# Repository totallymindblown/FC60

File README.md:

# **FC60**
A simple Feeder Controller for electric SMT-Feeders.

## Specifications
* reliable Atmel SAMC21N18A MCU
* single 24V Power Supply
* max. 60 Feeders can be controlled with one Board
* CAN-FD Interface (compatible with MB6HC, MB6XD, etc.)
* optional RS485 Interface
## Hardware
The board has been designed with [Kicad 8.0.4](https://www.kicad.org).  
All schematics, design-files, gerbers and bom can be found in [hardware](/hardware/).
## Software
A Bootloader and Firmware for use with e.g. RFF 3.5 can be found in [Releases](http://github.com/totallymindblown/FC60/releases/latest).  

First the bootloader needs to be programmed with a suitable programmer (e.g. ATMEL-ICE, SEGGER J-Link, etc.) using the SWD-Interface J61 (10-pin 50mil connector), then the firmware can be uploaded from the mainboard. Since the MCU runs with 5V, the programmer must support this target voltage.
## How to Use
The feeders are each connected using connector J1..J60 and supplied with 24V. The trigger signal is provided by a short pulse (1 ms) to the control input of the feeder.
An appropriately dimensioned 24V switching power supply is connected to J64.

To be able to trigger the feeders, a single GPIO pin must be created for the FC60 using the following gcode example. The port number and CAN address are selected according to the application.

*_create Port 12 on FC60 with CAN address 24 :_* <b>`M950 P12 C"24.feeder"`</b>

The feeder is selected using <b>M42</b> with the <b>S</b> parameter, but it has here nothing to do with PWM. It is just a simple way on the FC60 to circumvent the RFF GPIO limit.  

*_trigger feeder number 1 :_* <b>`M42 P12 S1`</b>  

*_trigger feeder number 60 :_* <b>`M42 P12 S60`</b>  

The default CAN address of the FC60 is 124 which can be reset using JP2 (__CAN-RES__).  
CAN bus termination can be set with jumper JP1 (__TERM.__).

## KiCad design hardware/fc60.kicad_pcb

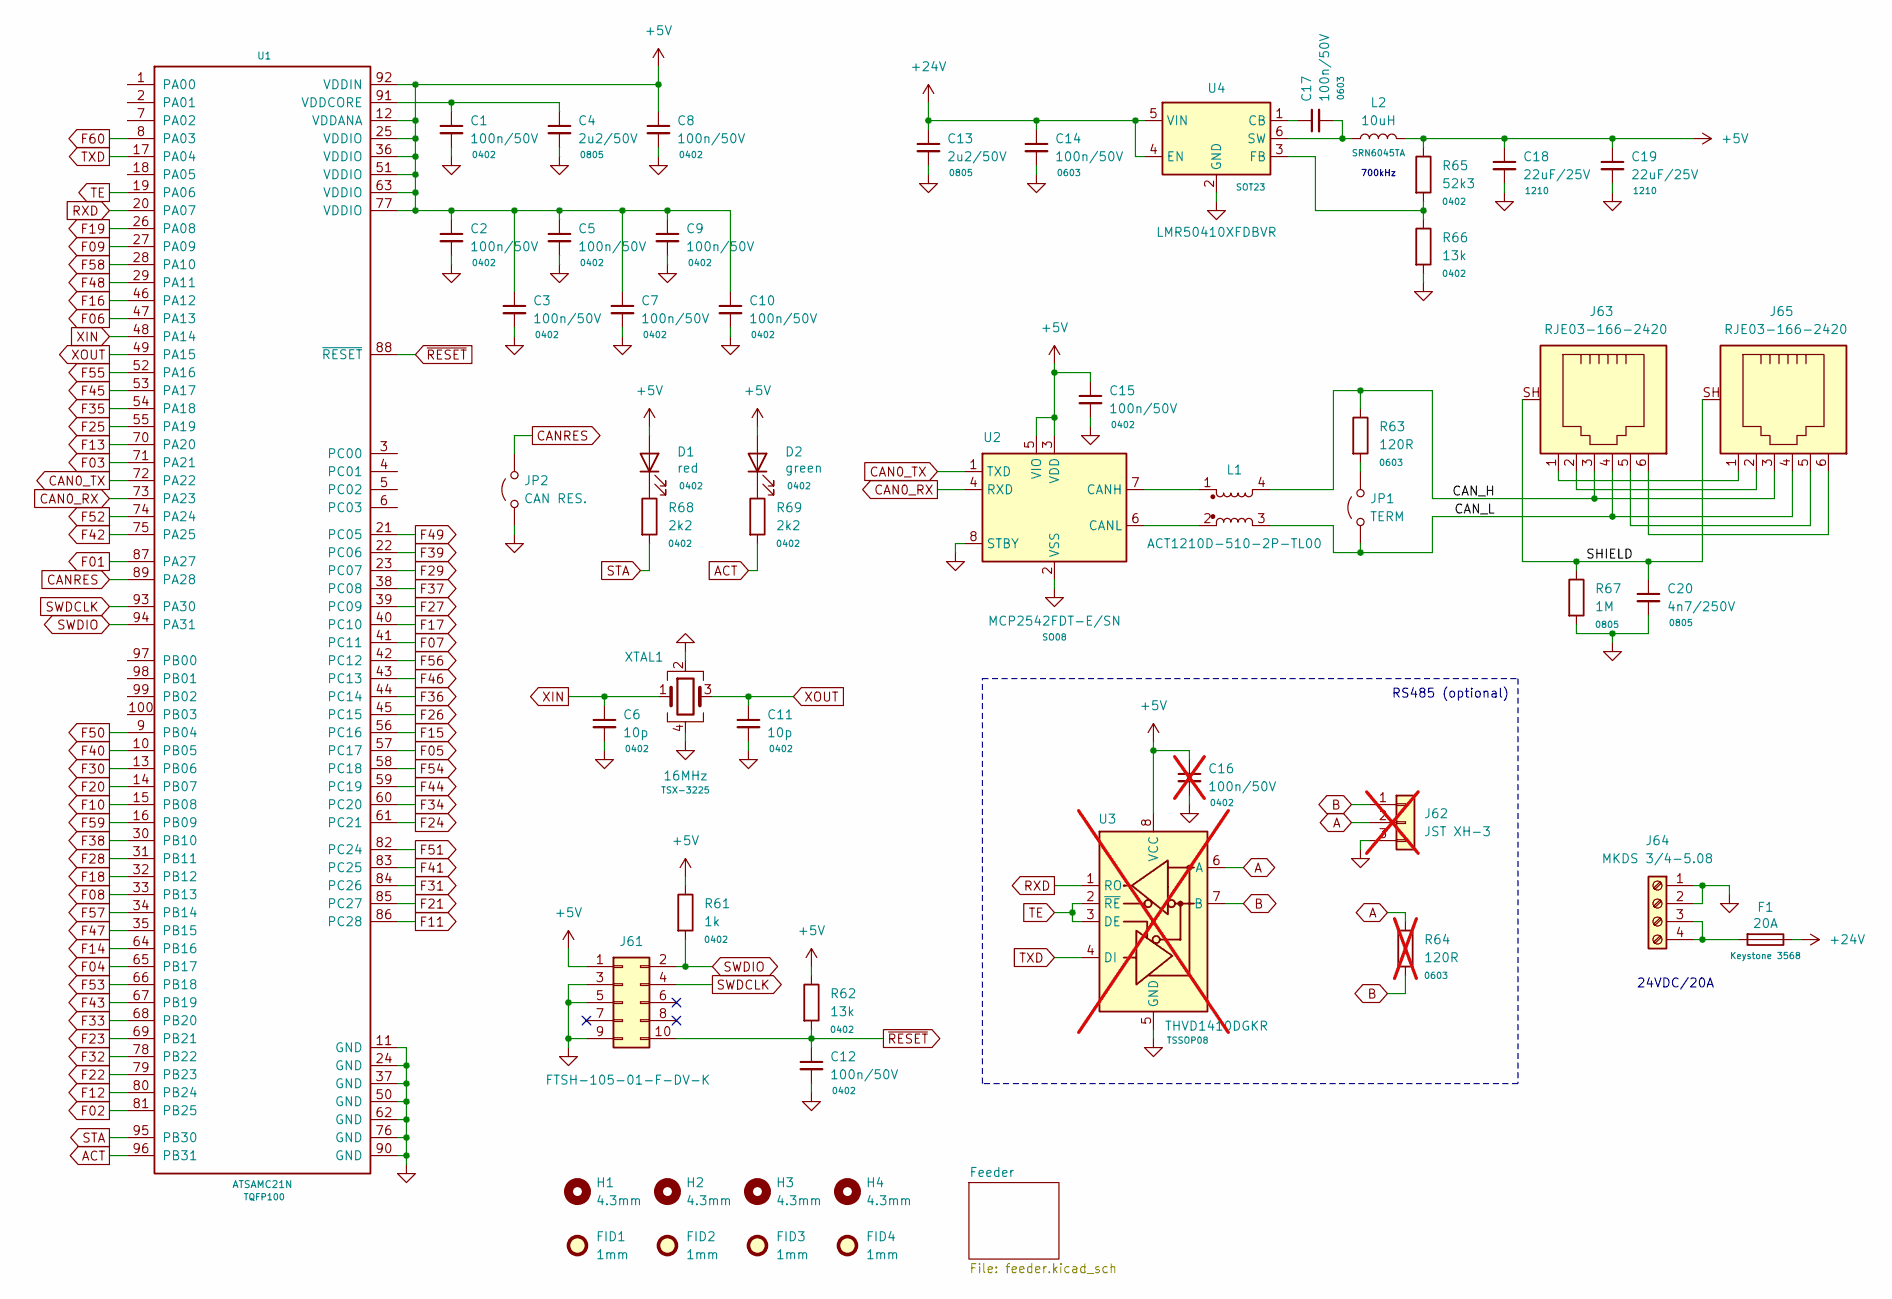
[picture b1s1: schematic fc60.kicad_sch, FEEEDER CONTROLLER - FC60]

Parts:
C1, C2, C3, C5, C7, C8, C9, C10, C12, C15: 100n/50V; C_0402_1005Metric
C4, C13: 2u2/50V; C_0805_2012Metric
C6, C11: 10p; C_0402_1005Metric
C14, C17: 100n/50V; C_0603_1608Metric
C16: 100n/50V; C_0402_1005Metric; not fitted
C18, C19: 22uF/25V; C_1210_3225Metric
C20: 4n7/250V; C_0805_2012Metric
D1: red; LED_0402_1005Metric
D2: green; LED_0402_1005Metric
F1: 20A; Fuseholder_Blade_Mini_Keystone_3568
FID1, FID2, FID3, FID4: 1mm; Fiducial_1mm_Mask2mm
H1, H2, H3, H4: 4.3mm; MountingHole_4.3mm_M4_ISO7380_Pad
J61: FTSH-105-01-F-DV-K; Samtec_SFH-105-01-F-D-K-TR
J62: JST XH-3; JST_XH_B3B-XH-A_1x03_P2.50mm_Vertical; not fitted
J63, J65: RJE03-166-2420; RJ25_Amphenol_RJE031662x20
J64: MKDS 3/4-5.08; TerminalBlock_Phoenix_MKDS-3-4-5.08_1x04_P5.08mm_Horizontal
JP1: TERM; PinHeader_1x02_P2.54mm_Vertical
JP2: CAN RES.; PinHeader_1x02_P2.54mm_Vertical
L1: ACT1210D-510-2P-TL00; L_CommonModeChoke_TDK_ACT1210D
L2: 10uH; L_Bourns_SRN6045TA
R61: 1k; R_0402_1005Metric
R62, R66: 13k; R_0402_1005Metric
R63: 120R; R_0603_1608Metric
R64: 120R; R_0603_1608Metric; not fitted
R65: 52k3; R_0402_1005Metric
R67: 1M; R_0805_2012Metric
R68, R69: 2k2; R_0402_1005Metric
U1: ATSAMC21N; TQFP-100_14x14mm_P0.5mm
U2: MCP2542FDT-E/SN; SO-8_3.9x4.9mm_P1.27mm
U3: THVD1410DGKR; TSSOP-8_3x3mm_P0.65mm; not fitted
U4: LMR50410XFDBVR; SOT-23-6
XTAL1: 16MHz; Crystal_SMD_SeikoEpson_TSX3225-4Pin_3.2x2.5mm

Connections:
+5V: C2.1, C3.1, C5.1, C7.1, C8.1, C9.1, C10.1, C15.1, C16.1, C18.1, C19.1, D1.2 (A), D2.2 (A), J61.1, L2.2, R61.1, R62.1, R65.1, U1.12 (VDDANA), U1.25 (VDDIO), U1.36 (VDDIO), U1.51 (VDDIO), U1.63 (VDDIO), U1.77 (VDDIO), U1.92 (VDDIN), U2.3 (VDD), U2.5 (VIO), U3.8 (VCC)
+24V: C13.1, C14.1, F1.1, U4.4 (EN), U4.5 (VIN); also elsewhere on the board
/CAN_H: J63.3, J65.3, L1.4, R63.1
/CAN_L: J63.4, J65.4, JP1.1 (A), L1.3
/SHIELD: C20.1, J63.SH, J65.SH, R67.1
A: J62.2, R64.1, U3.6 (A)
ACT: R69.2, U1.96 (PB31)
B: J62.1, R64.2, U3.7 (B)
CAN0_RX: U1.73 (PA23), U2.4 (RXD)
CAN0_TX: U1.72 (PA22), U2.1 (TXD)
CANRES: JP2.2 (B), U1.89 (PA28)
F01: U1.87 (PA27); also elsewhere on the board
F02: U1.81 (PB25); also elsewhere on the board
F03: U1.71 (PA21); also elsewhere on the board
F04: U1.65 (PB17); also elsewhere on the board
F05: U1.57 (PC17); also elsewhere on the board
F06: U1.47 (PA13); also elsewhere on the board
F07: U1.41 (PC11); also elsewhere on the board
F08: U1.33 (PB13); also elsewhere on the board
F09: U1.27 (PA09); also elsewhere on the board
F10: U1.15 (PB08); also elsewhere on the board
F11: U1.86 (PC28); also elsewhere on the board
F12: U1.80 (PB24); also elsewhere on the board
F13: U1.70 (PA20); also elsewhere on the board
F14: U1.64 (PB16); also elsewhere on the board
F15: U1.56 (PC16); also elsewhere on the board
F16: U1.46 (PA12); also elsewhere on the board
F17: U1.40 (PC10); also elsewhere on the board
F18: U1.32 (PB12); also elsewhere on the board
F19: U1.26 (PA08); also elsewhere on the board
F20: U1.14 (PB07); also elsewhere on the board
F21: U1.85 (PC27); also elsewhere on the board
F22: U1.79 (PB23); also elsewhere on the board
F23: U1.69 (PB21); also elsewhere on the board
F24: U1.61 (PC21); also elsewhere on the board
F25: U1.55 (PA19); also elsewhere on the board
F26: U1.45 (PC15); also elsewhere on the board
F27: U1.39 (PC09); also elsewhere on the board
F28: U1.31 (PB11); also elsewhere on the board
F29: U1.23 (PC07); also elsewhere on the board
F30: U1.13 (PB06); also elsewhere on the board
F31: U1.84 (PC26); also elsewhere on the board
F32: U1.78 (PB22); also elsewhere on the board
F33: U1.68 (PB20); also elsewhere on the board
F34: U1.60 (PC20); also elsewhere on the board
F35: U1.54 (PA18); also elsewhere on the board
F36: U1.44 (PC14); also elsewhere on the board
F37: U1.38 (PC08); also elsewhere on the board
F38: U1.30 (PB10); also elsewhere on the board
F39: U1.22 (PC06); also elsewhere on the board
F40: U1.10 (PB05); also elsewhere on the board
F41: U1.83 (PC25); also elsewhere on the board
F42: U1.75 (PA25); also elsewhere on the board
F43: U1.67 (PB19); also elsewhere on the board
F44: U1.59 (PC19); also elsewhere on the board
F45: U1.53 (PA17); also elsewhere on the board
F46: U1.43 (PC13); also elsewhere on the board
F47: U1.35 (PB15); also elsewhere on the board
F48: U1.29 (PA11); also elsewhere on the board
F49: U1.21 (PC05); also elsewhere on the board
F50: U1.9 (PB04); also elsewhere on the board
F51: U1.82 (PC24); also elsewhere on the board
F52: U1.74 (PA24); also elsewhere on the board
F53: U1.66 (PB18); also elsewhere on the board
F54: U1.58 (PC18); also elsewhere on the board
F55: U1.52 (PA16); also elsewhere on the board
F56: U1.42 (PC12); also elsewhere on the board
F57: U1.34 (PB14); also elsewhere on the board
F58: U1.28 (PA10); also elsewhere on the board
F59: U1.16 (PB09); also elsewhere on the board
F60: U1.8 (PA03); also elsewhere on the board
GND: C1.2, C2.2, C3.2, C4.2, C5.2, C6.2, C7.2, C8.2, C9.2, C10.2, C11.2, C12.2, C13.2, C14.2, C15.2, C16.2, C18.2, C19.2, C20.2, J61.3, J61.5, J61.9, J62.3, J64.1, J64.2, JP2.1 (A), R66.2, R67.2, U1.11 (GND), U1.24 (GND), U1.37 (GND), U1.50 (GND), U1.62 (GND), U1.76 (GND), U1.90 (GND), U2.2 (VSS), U2.8 (STBY), U3.5 (GND), U4.2 (GND), XTAL1.2, XTAL1.4; also elsewhere on the board
unnamed: D1.1 (K), R68.1
unnamed: D2.1 (K), R69.1
unnamed: J63.1, J65.1
unnamed: J63.2, J65.2
unnamed: J63.5, J65.5
unnamed: J63.6, J65.6
unnamed: F1.2, J64.3, J64.4
unnamed: JP1.2 (B), R63.2
unnamed: C1.1, C4.1, U1.91 (VDDCORE)
unnamed: L1.1, U2.7 (CANH)
unnamed: L1.2, U2.6 (CANL)
unnamed: C17.1, U4.1 (CB)
unnamed: R65.2, R66.1, U4.3 (FB)
unnamed: C17.2, L2.1, U4.6 (SW)
RXD: U1.20 (PA07), U3.1 (RO)
STA: R68.2, U1.95 (PB30)
SWDCLK: J61.4, U1.93 (PA30)
SWDIO: J61.2, R61.2, U1.94 (PA31)
TE: U1.19 (PA06), U3.2 (~RE), U3.3 (DE)
TXD: U1.17 (PA04), U3.4 (DI)
XIN: C6.1, U1.48 (PA14), XTAL1.1
XOUT: C11.1, U1.49 (PA15), XTAL1.3
~RESET: C12.1, J61.10, R62.2, U1.88 (~RESET)

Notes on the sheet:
24VDC/20A
RS485 (optional)
700kHz

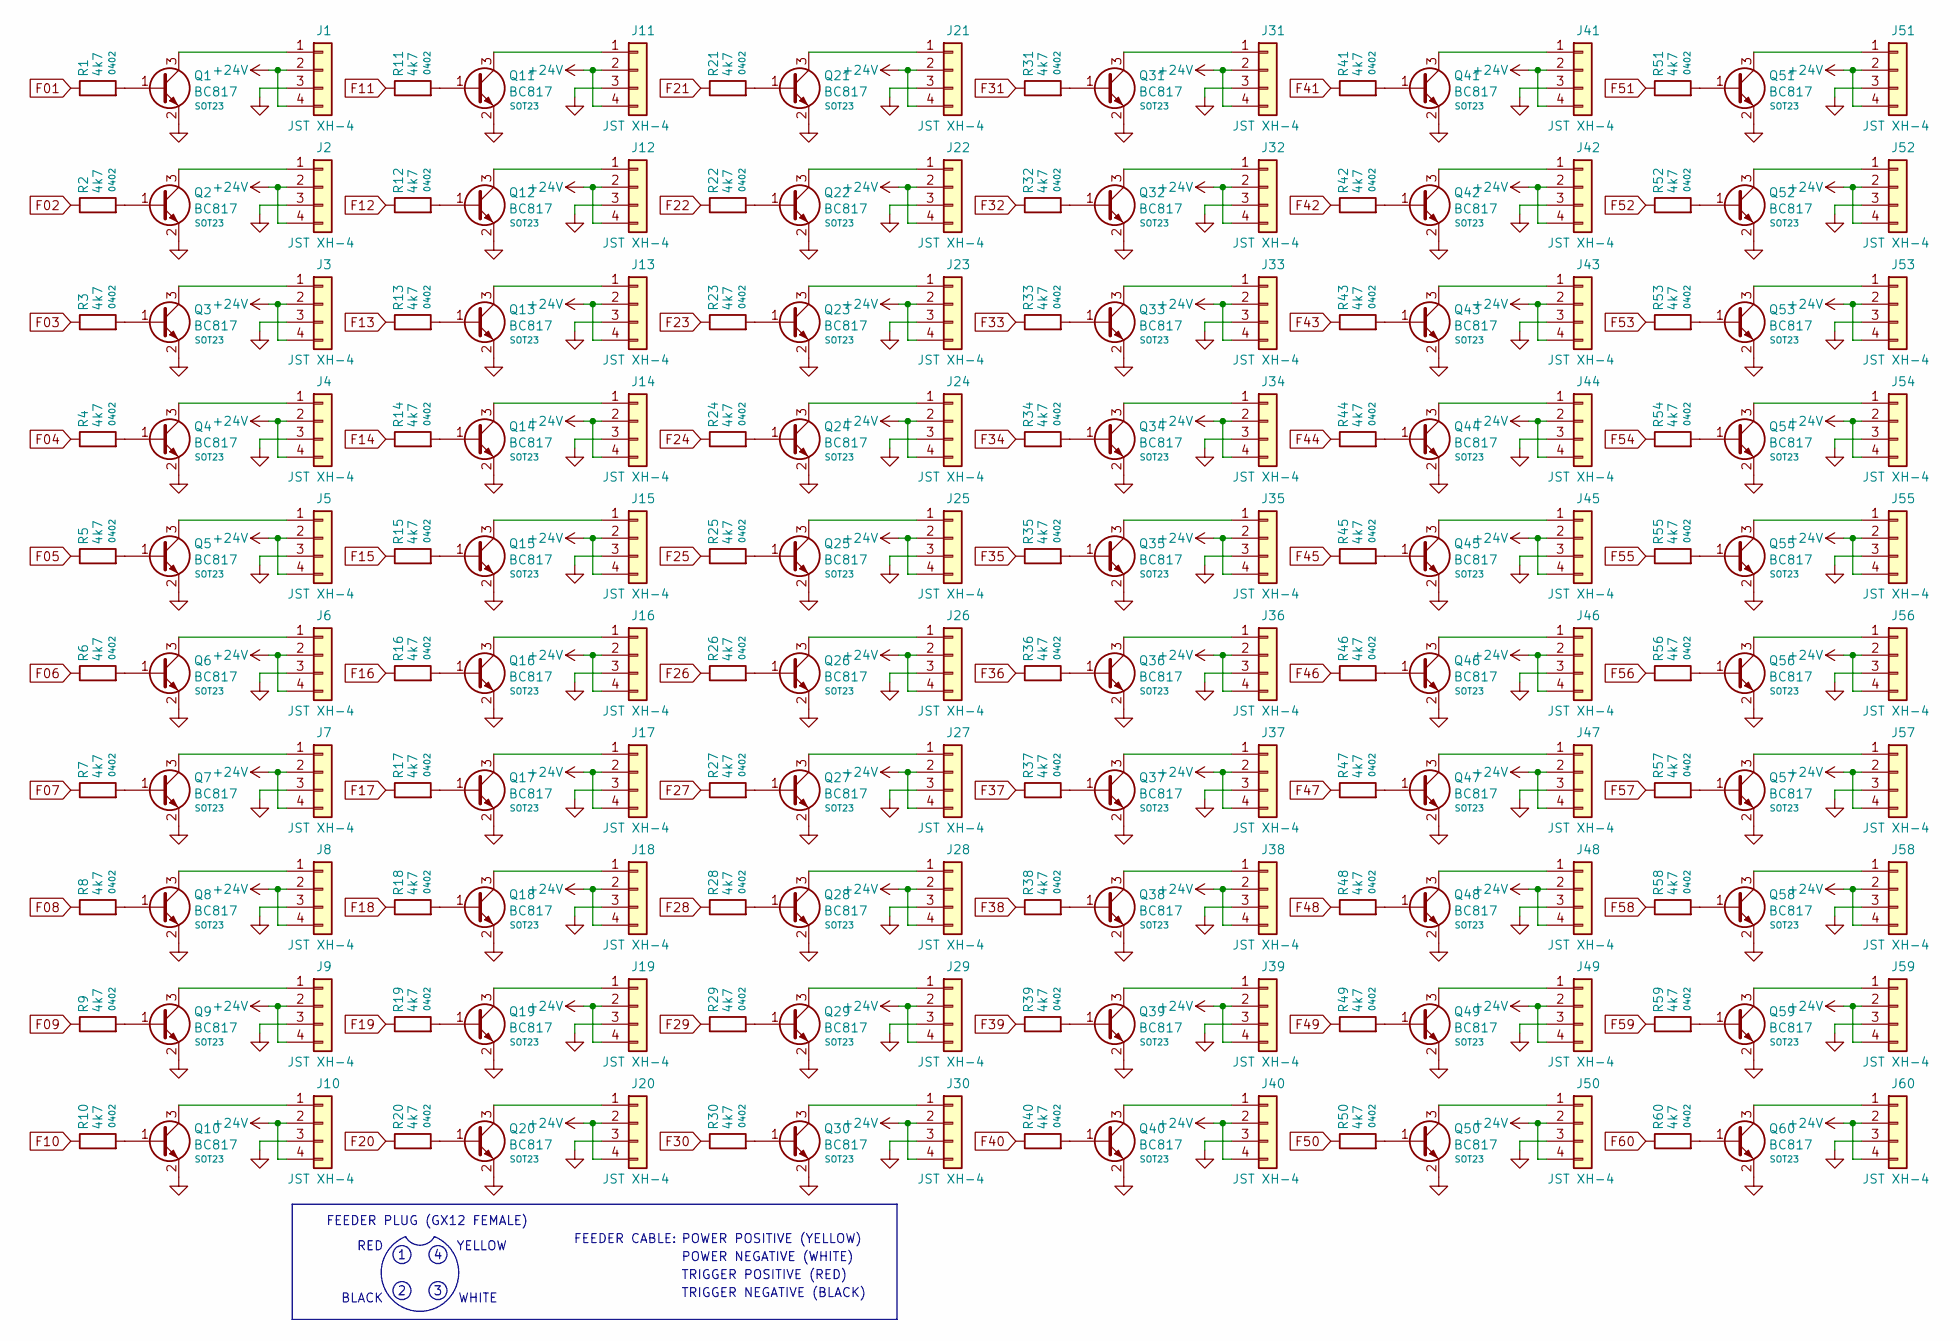
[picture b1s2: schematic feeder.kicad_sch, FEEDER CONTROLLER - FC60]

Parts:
J1, J2, J3, J4, J5, J6, J7, J8, J9, J10, J11, J12, J13, J14, J15, J16, J17, J18, J19, J20, J21, J22, J23, J24, J25, J26, J27, J28, J29, J30, J31, J32, J33, J34, J35, J36, J37, J38, J39, J40, J41, J42, J43, J44, J45, J46, J47, J48, J49, J50, J51, J52, J53, J54, J55, J56, J57, J58, J59, J60: JST XH-4; JST_XH_B4B-XH-A_1x04_P2.50mm_Vertical
Q1, Q2, Q3, Q4, Q5, Q6, Q7, Q8, Q9, Q10, Q11, Q12, Q13, Q14, Q15, Q16, Q17, Q18, Q19, Q20, Q21, Q22, Q23, Q24, Q25, Q26, Q27, Q28, Q29, Q30, Q31, Q32, Q33, Q34, Q35, Q36, Q37, Q38, Q39, Q40, Q41, Q42, Q43, Q44, Q45, Q46, Q47, Q48, Q49, Q50, Q51, Q52, Q53, Q54, Q55, Q56, Q57, Q58, Q59, Q60: BC817; SOT-23
R1, R2, R3, R4, R5, R6, R7, R8, R9, R10, R11, R12, R13, R14, R15, R16, R17, R18, R19, R20, R21, R22, R23, R24, R25, R26, R27, R28, R29, R30, R31, R32, R33, R34, R35, R36, R37, R38, R39, R40, R41, R42, R43, R44, R45, R46, R47, R48, R49, R50, R51, R52, R53, R54, R55, R56, R57, R58, R59, R60: 4k7; R_0402_1005Metric

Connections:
+24V: J1.2, J1.4, J2.2, J2.4, J3.2, J3.4, J4.2, J4.4, J5.2, J5.4, J6.2, J6.4, J7.2, J7.4, J8.2, J8.4, J9.2, J9.4, J10.2, J10.4, J11.2, J11.4, J12.2, J12.4, J13.2, J13.4, J14.2, J14.4, J15.2, J15.4, J16.2, J16.4, J17.2, J17.4, J18.2, J18.4, J19.2, J19.4, J20.2, J20.4, J21.2, J21.4, J22.2, J22.4, J23.2, J23.4, J24.2, J24.4, J25.2, J25.4, J26.2, J26.4, J27.2, J27.4, J28.2, J28.4, J29.2, J29.4, J30.2, J30.4, J31.2, J31.4, J32.2, J32.4, J33.2, J33.4, J34.2, J34.4, J35.2, J35.4, J36.2, J36.4, J37.2, J37.4, J38.2, J38.4, J39.2, J39.4, J40.2, J40.4, J41.2, J41.4, J42.2, J42.4, J43.2, J43.4, J44.2, J44.4, J45.2, J45.4, J46.2, J46.4, J47.2, J47.4, J48.2, J48.4, J49.2, J49.4, J50.2, J50.4, J51.2, J51.4, J52.2, J52.4, J53.2, J53.4, J54.2, J54.4, J55.2, J55.4, J56.2, J56.4, J57.2, J57.4, J58.2, J58.4, J59.2, J59.4, J60.2, J60.4; also elsewhere on the board
F01: R1.1; also elsewhere on the board
F02: R2.1; also elsewhere on the board
F03: R3.1; also elsewhere on the board
F04: R4.1; also elsewhere on the board
F05: R5.1; also elsewhere on the board
F06: R6.1; also elsewhere on the board
F07: R7.1; also elsewhere on the board
F08: R8.1; also elsewhere on the board
F09: R9.1; also elsewhere on the board
F10: R10.1; also elsewhere on the board
F11: R11.1; also elsewhere on the board
F12: R12.1; also elsewhere on the board
F13: R13.1; also elsewhere on the board
F14: R14.1; also elsewhere on the board
F15: R15.1; also elsewhere on the board
F16: R16.1; also elsewhere on the board
F17: R17.1; also elsewhere on the board
F18: R18.1; also elsewhere on the board
F19: R19.1; also elsewhere on the board
F20: R20.1; also elsewhere on the board
F21: R21.1; also elsewhere on the board
F22: R22.1; also elsewhere on the board
F23: R23.1; also elsewhere on the board
F24: R24.1; also elsewhere on the board
F25: R25.1; also elsewhere on the board
F26: R26.1; also elsewhere on the board
F27: R27.1; also elsewhere on the board
F28: R28.1; also elsewhere on the board
F29: R29.1; also elsewhere on the board
F30: R30.1; also elsewhere on the board
F31: R31.1; also elsewhere on the board
F32: R32.1; also elsewhere on the board
F33: R33.1; also elsewhere on the board
F34: R34.1; also elsewhere on the board
F35: R35.1; also elsewhere on the board
F36: R36.1; also elsewhere on the board
F37: R37.1; also elsewhere on the board
F38: R38.1; also elsewhere on the board
F39: R39.1; also elsewhere on the board
F40: R40.1; also elsewhere on the board
F41: R41.1; also elsewhere on the board
F42: R42.1; also elsewhere on the board
F43: R43.1; also elsewhere on the board
F44: R44.1; also elsewhere on the board
F45: R45.1; also elsewhere on the board
F46: R46.1; also elsewhere on the board
F47: R47.1; also elsewhere on the board
F48: R48.1; also elsewhere on the board
F49: R49.1; also elsewhere on the board
F50: R50.1; also elsewhere on the board
F51: R51.1; also elsewhere on the board
F52: R52.1; also elsewhere on the board
F53: R53.1; also elsewhere on the board
F54: R54.1; also elsewhere on the board
F55: R55.1; also elsewhere on the board
F56: R56.1; also elsewhere on the board
F57: R57.1; also elsewhere on the board
F58: R58.1; also elsewhere on the board
F59: R59.1; also elsewhere on the board
F60: R60.1; also elsewhere on the board
GND: J1.3, J2.3, J3.3, J4.3, J5.3, J6.3, J7.3, J8.3, J9.3, J10.3, J11.3, J12.3, J13.3, J14.3, J15.3, J16.3, J17.3, J18.3, J19.3, J20.3, J21.3, J22.3, J23.3, J24.3, J25.3, J26.3, J27.3, J28.3, J29.3, J30.3, J31.3, J32.3, J33.3, J34.3, J35.3, J36.3, J37.3, J38.3, J39.3, J40.3, J41.3, J42.3, J43.3, J44.3, J45.3, J46.3, J47.3, J48.3, J49.3, J50.3, J51.3, J52.3, J53.3, J54.3, J55.3, J56.3, J57.3, J58.3, J59.3, J60.3, Q1.2 (E), Q2.2 (E), Q3.2 (E), Q4.2 (E), Q5.2 (E), Q6.2 (E), Q7.2 (E), Q8.2 (E), Q9.2 (E), Q10.2 (E), Q11.2 (E), Q12.2 (E), Q13.2 (E), Q14.2 (E), Q15.2 (E), Q16.2 (E), Q17.2 (E), Q18.2 (E), Q19.2 (E), Q20.2 (E), Q21.2 (E), Q22.2 (E), Q23.2 (E), Q24.2 (E), Q25.2 (E), Q26.2 (E), Q27.2 (E), Q28.2 (E), Q29.2 (E), Q30.2 (E), Q31.2 (E), Q32.2 (E), Q33.2 (E), Q34.2 (E), Q35.2 (E), Q36.2 (E), Q37.2 (E), Q38.2 (E), Q39.2 (E), Q40.2 (E), Q41.2 (E), Q42.2 (E), Q43.2 (E), Q44.2 (E), Q45.2 (E), Q46.2 (E), Q47.2 (E), Q48.2 (E), Q49.2 (E), Q50.2 (E), Q51.2 (E), Q52.2 (E), Q53.2 (E), Q54.2 (E), Q55.2 (E), Q56.2 (E), Q57.2 (E), Q58.2 (E), Q59.2 (E), Q60.2 (E); also elsewhere on the board
unnamed: J1.1, Q1.3 (C)
unnamed: J2.1, Q2.3 (C)
unnamed: J3.1, Q3.3 (C)
unnamed: J4.1, Q4.3 (C)
unnamed: J5.1, Q5.3 (C)
unnamed: J6.1, Q6.3 (C)
unnamed: J7.1, Q7.3 (C)
unnamed: J8.1, Q8.3 (C)
unnamed: J9.1, Q9.3 (C)
unnamed: J10.1, Q10.3 (C)
unnamed: J11.1, Q11.3 (C)
unnamed: J12.1, Q12.3 (C)
unnamed: J13.1, Q13.3 (C)
unnamed: J14.1, Q14.3 (C)
unnamed: J15.1, Q15.3 (C)
unnamed: J16.1, Q16.3 (C)
unnamed: J17.1, Q17.3 (C)
unnamed: J18.1, Q18.3 (C)
unnamed: J19.1, Q19.3 (C)
unnamed: J20.1, Q20.3 (C)
unnamed: J21.1, Q21.3 (C)
unnamed: J22.1, Q22.3 (C)
unnamed: J23.1, Q23.3 (C)
unnamed: J24.1, Q24.3 (C)
unnamed: J25.1, Q25.3 (C)
unnamed: J26.1, Q26.3 (C)
unnamed: J27.1, Q27.3 (C)
unnamed: J28.1, Q28.3 (C)
unnamed: J29.1, Q29.3 (C)
unnamed: J30.1, Q30.3 (C)
unnamed: J31.1, Q31.3 (C)
unnamed: J32.1, Q32.3 (C)
unnamed: J33.1, Q33.3 (C)
unnamed: J34.1, Q34.3 (C)
unnamed: J35.1, Q35.3 (C)
unnamed: J36.1, Q36.3 (C)
unnamed: J37.1, Q37.3 (C)
unnamed: J38.1, Q38.3 (C)
unnamed: J39.1, Q39.3 (C)
unnamed: J40.1, Q40.3 (C)
unnamed: J41.1, Q41.3 (C)
unnamed: J42.1, Q42.3 (C)
unnamed: J43.1, Q43.3 (C)
unnamed: J44.1, Q44.3 (C)
unnamed: J45.1, Q45.3 (C)
unnamed: J46.1, Q46.3 (C)
unnamed: J47.1, Q47.3 (C)
unnamed: J48.1, Q48.3 (C)
unnamed: J49.1, Q49.3 (C)
unnamed: J50.1, Q50.3 (C)
unnamed: J51.1, Q51.3 (C)
unnamed: J52.1, Q52.3 (C)
unnamed: J53.1, Q53.3 (C)
unnamed: J54.1, Q54.3 (C)
unnamed: J55.1, Q55.3 (C)
unnamed: J56.1, Q56.3 (C)
unnamed: J57.1, Q57.3 (C)
unnamed: J58.1, Q58.3 (C)
unnamed: J59.1, Q59.3 (C)
unnamed: J60.1, Q60.3 (C)
unnamed: Q1.1 (B), R1.2
unnamed: Q2.1 (B), R2.2
unnamed: Q3.1 (B), R3.2
unnamed: Q4.1 (B), R4.2
unnamed: Q5.1 (B), R5.2
unnamed: Q6.1 (B), R6.2
unnamed: Q7.1 (B), R7.2
unnamed: Q8.1 (B), R8.2
unnamed: Q9.1 (B), R9.2
unnamed: Q10.1 (B), R10.2
unnamed: Q11.1 (B), R11.2
unnamed: Q12.1 (B), R12.2
unnamed: Q13.1 (B), R13.2
unnamed: Q14.1 (B), R14.2
unnamed: Q15.1 (B), R15.2
unnamed: Q16.1 (B), R16.2
unnamed: Q17.1 (B), R17.2
unnamed: Q18.1 (B), R18.2
unnamed: Q19.1 (B), R19.2
unnamed: Q20.1 (B), R20.2
unnamed: Q21.1 (B), R21.2
unnamed: Q22.1 (B), R22.2
unnamed: Q23.1 (B), R23.2
unnamed: Q24.1 (B), R24.2
unnamed: Q25.1 (B), R25.2
unnamed: Q26.1 (B), R26.2
unnamed: Q27.1 (B), R27.2
unnamed: Q28.1 (B), R28.2
unnamed: Q29.1 (B), R29.2
unnamed: Q30.1 (B), R30.2
unnamed: Q31.1 (B), R31.2
unnamed: Q32.1 (B), R32.2
unnamed: Q33.1 (B), R33.2
unnamed: Q34.1 (B), R34.2
unnamed: Q35.1 (B), R35.2
unnamed: Q36.1 (B), R36.2
unnamed: Q37.1 (B), R37.2
unnamed: Q38.1 (B), R38.2
unnamed: Q39.1 (B), R39.2
unnamed: Q40.1 (B), R40.2
unnamed: Q41.1 (B), R41.2
unnamed: Q42.1 (B), R42.2
unnamed: Q43.1 (B), R43.2
unnamed: Q44.1 (B), R44.2
unnamed: Q45.1 (B), R45.2
unnamed: Q46.1 (B), R46.2
unnamed: Q47.1 (B), R47.2
unnamed: Q48.1 (B), R48.2
unnamed: Q49.1 (B), R49.2
unnamed: Q50.1 (B), R50.2
unnamed: Q51.1 (B), R51.2
unnamed: Q52.1 (B), R52.2
unnamed: Q53.1 (B), R53.2
unnamed: Q54.1 (B), R54.2
unnamed: Q55.1 (B), R55.2
unnamed: Q56.1 (B), R56.2
unnamed: Q57.1 (B), R57.2
unnamed: Q58.1 (B), R58.2
unnamed: Q59.1 (B), R59.2
unnamed: Q60.1 (B), R60.2

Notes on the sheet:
FEEDER PLUG (GX12 FEMALE)
FEEDER CABLE:
POWER POSITIVE (YELLOW)
RED
TRIGGER NEGATIVE (BLACK)
TRIGGER POSITIVE (RED)
BLACK
YELLOW
POWER NEGATIVE (WHITE)
WHITE

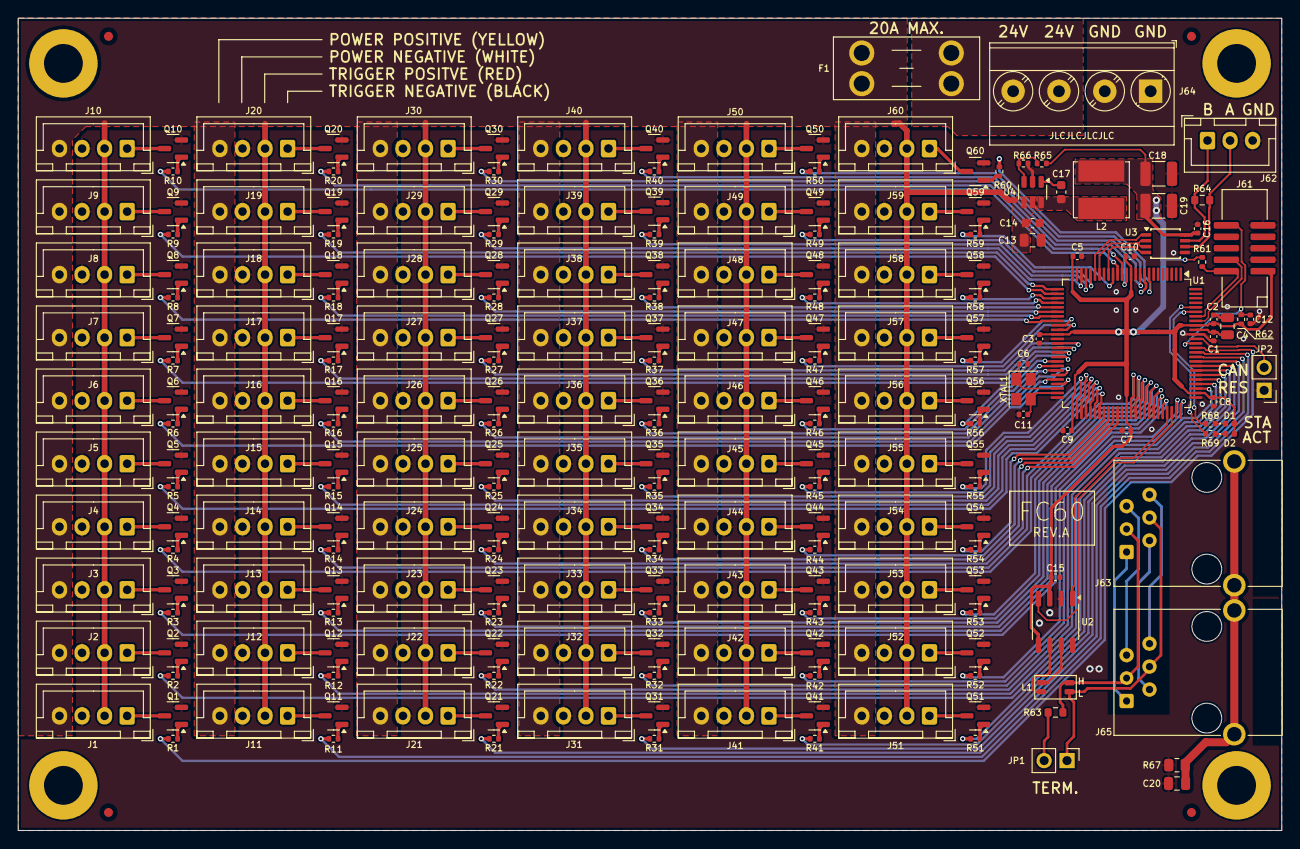
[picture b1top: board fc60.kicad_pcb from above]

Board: 2 copper layers, 140.0 x 90.0 mm, 234 parts (0 on the bottom side), 215 nets.
